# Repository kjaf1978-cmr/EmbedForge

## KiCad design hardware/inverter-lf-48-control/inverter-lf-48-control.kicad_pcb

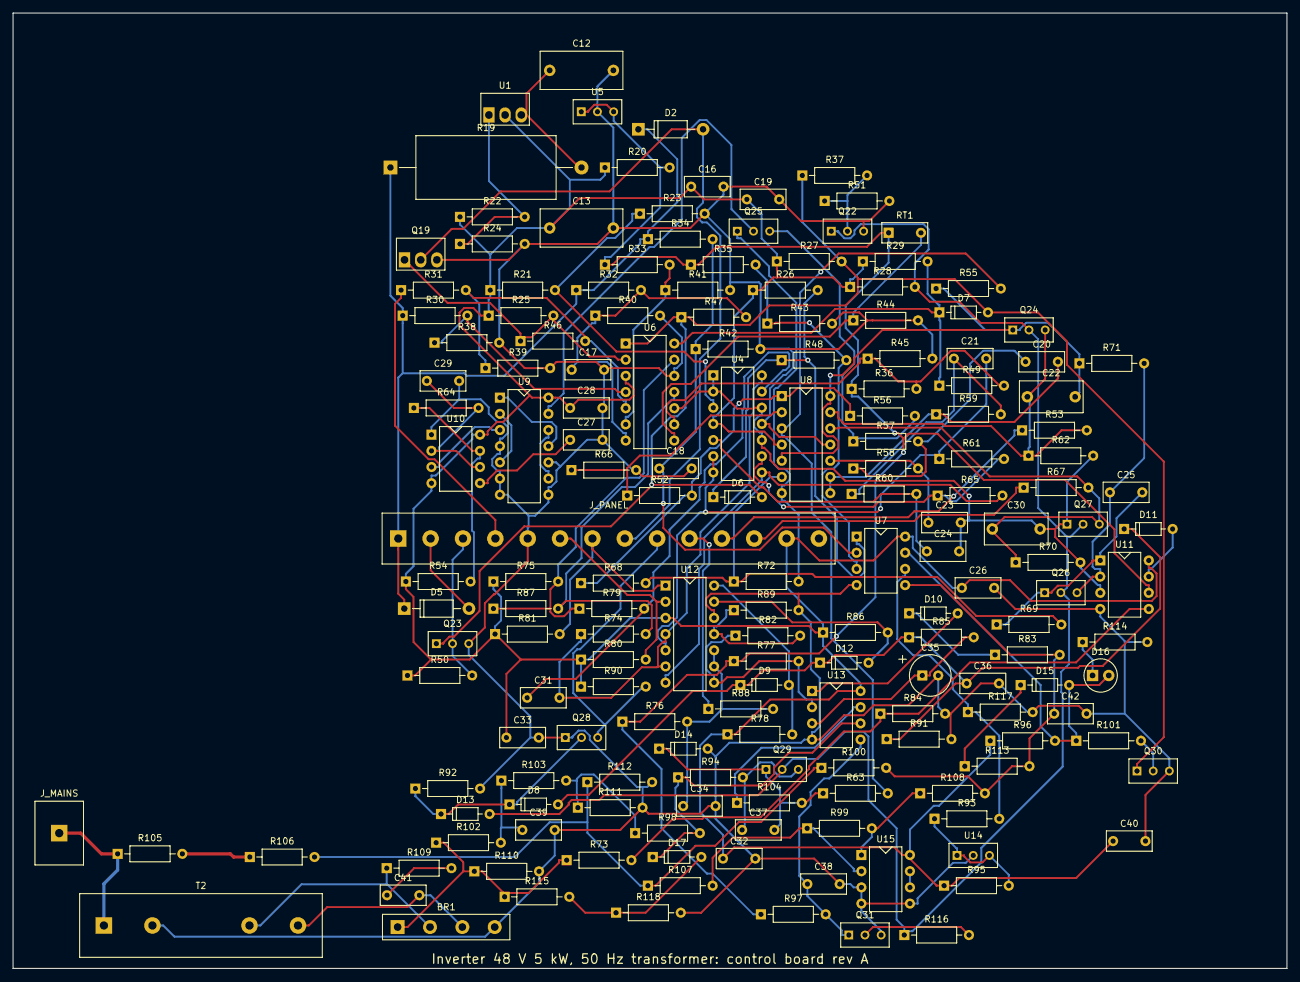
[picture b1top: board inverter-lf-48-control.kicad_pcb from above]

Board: 2 copper layers, 200.0 x 150.0 mm, 172 parts (0 on the bottom side), 101 nets.

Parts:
BR1: DB107; Bridge_Inline_4
C12: 2.2u; C_Film_P10
C13: 10u; C_Film_P10
C16, C19, C23, C26, C28, C29, C32, C33, C40, C41: 100n; C_Disc_5.08
C17, C18, C38: 470n; C_Disc_5.08
C20: 110n; C_Disc_5.08
C21: 270n; C_Disc_5.08
C22, C30: 3.3u; C_Film_P7.5
C24: 39n; C_Disc_5.08
C25, C39, C42: 1u; C_Disc_5.08
C27: 10n; C_Disc_5.08
C31: 3.3n; C_Disc_5.08
C34: 47p; C_Disc_5.08
C35: 22u; CP_Radial_D6.3
C36: 150p; C_Disc_5.08
C37: 220n; C_Disc_5.08
D2, D5: 1N4007; D_DO-41
D6, D7, D8, D9, D10, D11, D12, D13, D15, D17: 1N4148; D_DO-35
D14: BZX55C3V3; D_DO-35
D16: red; LED_D5.0
J_MAINS: mains to the panel; TerminalBlock_1x1_P7.62
J_PANEL: to the panel; TerminalBlock_1x14
Q19: IRF540N; TO-220_Vertical
Q22, Q23, Q30, Q31: BC547B; TO-92_Wide
Q24, Q25, Q26, Q27, Q28, Q29: 2N7000; TO-92_Wide
R19: 220; R_Cement_5W
R20, R78, R86, R95, R96: 2.2k; R_Axial_0207
R21, R23, R25, R26, R27, R28, R29, R38, R39, R40, R41, R42, R43, R44, R54, R61, R65, R66, R68, R69, R72, R74, R84, R88, R90, R101, R102, R112, R113, R117, R118: 10k; R_Axial_0207
R22: 240; R_Axial_0207
R24: 2.05k; R_Axial_0207
R30, R32, R63, R100: 200k; R_Axial_0207
R31: 182k; R_Axial_0207
R33: 1.54k; R_Axial_0207
R34: 243k; R_Axial_0207
R35: 715; R_Axial_0207
R36: 3.92k; R_Axial_0207
R37, R51, R62, R70, R94: 47k; R_Axial_0207
R45: 40.2k; R_Axial_0207
R46: 1M; R_Axial_0207
R47: 475k; R_Axial_0207
R48, R55, R91, R92, R97, R98, R99, R107, R108, R116: 100k; R_Axial_0207
R49: 2.2M; R_Axial_0207
R50: 22k; R_Axial_0207
R52: 4.99k; R_Axial_0207
R53, R67, R105, R106: 470k; R_Axial_0207
R56, R109: 220; R_Axial_0207
R57, R58, R59, R60: 22.1k; R_Axial_0207
R64: 30.9k; R_Axial_0207
R71: 33k; R_Axial_0207
R73: 54.9k; R_Axial_0207
R75, R104, R110: 1k; R_Axial_0207
R76: 90.9k; R_Axial_0207
R77: 86.6k; R_Axial_0207
R79: 13.3k; R_Axial_0207
R80, R81, R83, R114: 4.7k; R_Axial_0207
R82: 7.5k; R_Axial_0207
R85: 220k; R_Axial_0207
R87: 38.3k; R_Axial_0207
R89: 6.19k; R_Axial_0207
R93: 21.5k; R_Axial_0207
R103: 57.6k; R_Axial_0207
R111: 25.5k; R_Axial_0207
R115: 47.5k; R_Axial_0207
RT1: 10k; RT_Disc_5.08
T2: 0.052; Transformer_Wires_P7.62
U1: LM317HV; TO-220_Vertical
U4, U8: TL074; DIP-14
U5: TL431B; TO-92_Wide
U6, U12: LM339; DIP-14
U7: LM393; DIP-8
U9: V12; DIP-14
U10: NE555; DIP-8
U11, U13, U15: LM358; DIP-8
U14: TL431; TO-92_Wide

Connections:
ADJ: R22.2, R24.1, U1.1
AXA: D2.1, D5.1, J_PANEL.1, R19.1, R30.1, R32.1, R34.1
BF: D5.2, J_PANEL.2
BFL: Q30.2, R101.2
BKA: J_PANEL.3, Q23.2, R50.2
BQE: Q22.2, R37.2, R51.1
BSS: Q31.2, R116.2
BUS: J_PANEL.4, R31.1
C200: U9.3, U10.3
D50: R54.2, R64.1, U10.7
DV1: R105.2, R106.1
DVN: R100.1, R106.2, R107.1, R112.1
EN: D6.2, D7.2, Q23.1, Q30.1, R27.2, R37.1, R47.1, U6.1
ENN: D13.2, Q22.1, Q24.2, Q26.2, Q27.2, Q29.2, R28.2, R116.1
F1A: C20.1, R57.2, R58.1
F1B: C23.1, R58.2, U8.10
F1O: C20.2, R59.1, U8.8, U8.9
F2A: C21.1, R59.2, R60.1
F2B: C24.1, R60.2, U4.5
FEA: C37.1, Q29.3, R94.2
FLT: D15.2, D16.2, R96.2, R101.1, U7.7
GND: BR1.4, C12.2, C13.2, C16.2, C17.2, C18.2, C19.2, C26.2, C27.2, C28.2, C29.2, C32.2, C33.2, C34.2, C35.2, C36.2, C38.2, C39.2, C40.2, C42.2, D14.2, J_PANEL.5, Q19.3, Q22.3, Q23.3, Q28.1, Q30.3, Q31.3, R23.2, R24.2, R38.2, R39.2, R40.2, R41.2, R42.2, R43.2, R44.2, R45.2, R51.2, R66.2, R84.2, R89.2, R91.2, R92.2, R110.2, R111.2, R112.2, R114.2, R117.2, R118.2, T2.2, U4.11, U5.2, U6.12, U7.4, U8.11, U9.4, U9.6, U9.7, U9.8, U9.10, U10.1, U11.4, U12.12, U13.4, U14.2, U15.3, U15.4, U15.5
H: R52.2, R56.1, R68.1, U8.1
HN: R52.1, R66.1, U8.2
HP: R55.2, R63.2, U8.3
HVN: D6.1, R26.2, R48.1, U7.1
INA: J_PANEL.6, R80.2, U12.2
INB: J_PANEL.7, R81.2, U12.1
K50: C27.1, U10.5
KC: D2.2, J_PANEL.8, Q19.2
KEN: Q19.1, R25.2, R46.1, U6.2
L: Q25.1, R72.2, U8.7
LAT: D15.1, R113.1
LFA: D16.1, R114.1
LN: R68.2, R69.2, R72.1, U8.6
NDC: C22.1, Q24.3, R53.2, R62.1, U8.13
NEA: D17.1, R94.1, R98.2, U13.6
NFX: C25.1, Q26.3, R71.2, U11.2
NHS: R44.1, RT1.2, U6.8
NSB: R61.2, R65.1, U4.9
NTI: C31.1, R79.2, U4.13
OCH: R77.2, R82.1, U12.8, U13.2
OCL: R82.2, R89.1, U12.11
OCN: D12.2, R86.2, U12.13
OCP: D9.2, R78.2, U12.14
OCS: C36.1, D8.2, D9.1, D11.1, D12.1, R85.1, R91.1
OLC: C35.1, R85.2, U13.3
OLO: D10.2, U13.1
OLS: D10.1, R83.1
OUTL: J_MAINS.1, R105.1, T2.1
OVC: D11.2, U11.7
PDC: C30.1, Q27.3, R67.2, R70.1, U8.12
PLA: D17.2, R115.2, R118.1
PRN: R99.1, R107.2, U15.2
PRO: R99.2, R108.1, U15.1
PST: R74.2, R87.2, U6.11
Q50: Q25.2, U9.13
Q50N: U9.9, U9.12
Q100: U9.1, U9.11
Q100N: U9.2, U9.5
SAO: BR1.2, R109.1, T2.3
SBO: BR1.3, C41.2, T2.4
SD: J_PANEL.9, Q28.3, R90.2
SINE: C21.2, R61.1, U4.6, U4.7, U12.5
SINEB: R65.2, U4.8, U12.7
SNO: C41.1, R109.2
SO: R98.1, R103.2, R111.1
SP: C42.1, R83.2, R100.2, R108.2, R113.2, U7.5
SPRO: U15.6, U15.7
SQ: Q25.3, R56.2, R57.1
SQT: R75.2, R79.1, R87.1, U6.13
SRC: J_PANEL.10, R88.1
SRS: C34.1, R76.2, R88.2, U12.9, U12.10
STOP: D8.1, D13.1, Q28.2, R92.1
SWA: J_PANEL.11, R53.1
SWB: J_PANEL.12, R67.1
T50: C29.1, R64.2, U10.2, U10.6
T90: R36.2, R45.1, R49.2, U6.9
THN: D7.1, R29.2, R49.1, U6.14
TRI: C31.2, R74.1, U4.14, U12.4, U12.6
V12: C13.1, C16.1, C19.1, C26.1, C28.1, C32.1, C33.1, C40.1, J_PANEL.13, R20.1, R21.1, R22.1, R25.1, R26.1, R27.1, R28.1, R29.1, R50.1, R54.1, R75.1, R78.1, R80.1, R81.1, R86.1, R90.1, R95.1, R96.1, U1.2, U4.4, U6.3, U7.8, U8.4, U9.14, U10.4, U10.8, U11.8, U12.3, U13.8, U15.8
VA: C37.2, D14.1, Q29.1, R63.1, R104.2
VAO: R104.1, U13.7
VBF: R30.2, R38.1, U6.4
VBH: C18.1, R34.2, R42.1, U7.2
VBS: C17.1, R32.2, R40.1, R47.2, U6.7
VBU: R31.2, R39.1, R46.2, U6.5
VFX: C25.2, Q26.1, R69.1, U11.1
VHI: R35.2, R43.1, R48.2, U7.3
VLC: R73.2, R84.1, U11.5
VLO: R33.2, R41.1, U6.6
VME: C22.2, Q24.1, R55.1, R71.1, U8.5, U8.14
VMID: C23.2, C24.2, C30.2, Q27.1, R62.2, R70.2, U4.1, U4.2, U4.10, U4.12, U6.10, U11.3
VMR: R21.2, R23.1, U4.3
VRAW: C12.1, R19.2, U1.3
VREF: R20.2, R33.1, R35.1, R36.1, R76.1, R77.1, R97.1, RT1.1, U5.1, U5.3, U11.6
VREF2: R93.1, R95.2, U14.1, U14.3
VRO: BR1.1, R73.1, R102.1, R110.1, R115.1
VRP: R93.2, R117.1, U7.6
VSO: C39.1, R102.2, R103.1
VSS: C38.1, Q31.1, R97.2, U13.5

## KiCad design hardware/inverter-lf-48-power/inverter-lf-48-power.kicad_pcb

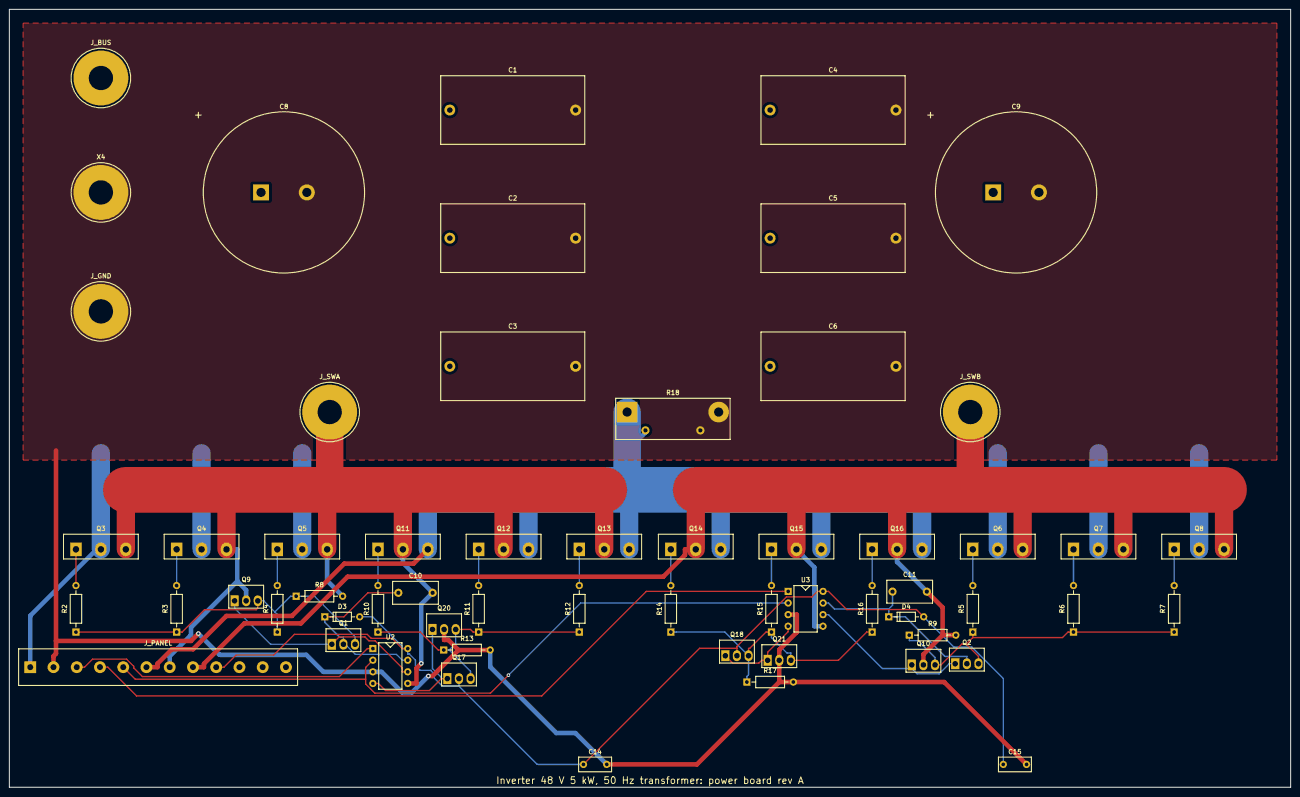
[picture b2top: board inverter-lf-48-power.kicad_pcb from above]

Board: 2 copper layers, 280.0 x 170.0 mm, 59 parts (0 on the bottom side), 31 nets.

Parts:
C1, C2, C3, C4, C5, C6: 47u; C_Film_P27.5
C8, C9: 2200u; CP_SnapIn_D35
C10, C11: 2.2u; C_Film_P7.5
C14, C15: 1u; C_Disc_5.08
D3, D4: 1N4148; D_DO-35
J_BUS: BUS; Lug_M5
J_GND: GND; Lug_M5
J_PANEL: to the panel; TerminalBlock_1x12
J_SWA: SWA; Lug_M5
J_SWB: SWB; Lug_M5
Q1, Q2, Q17, Q18: D44H11; TO-220_Vertical
Q3, Q4, Q5, Q6, Q7, Q8, Q11, Q12, Q13, Q14, Q15, Q16: IRFP4468; TO-247_Vertical
Q9, Q10, Q20, Q21: D45H11; TO-220_Vertical
R2, R3, R4, R5, R6, R7, R10, R11, R12, R14, R15, R16: 4.7; R_Axial_0207
R8, R9, R13, R17: 10k; R_Axial_0207
R18: 0.2m; R_Shunt_4T
U2, U3: IR2184-type 600 V; DIP-8
X4: BAT-; Lug_M5

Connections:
BUS: C1.1, C2.1, C3.1, C4.1, C5.1, C6.1, C8.1, C9.1, J_BUS.1, J_PANEL.1, Q3.2, Q4.2, Q5.2, Q6.2, Q7.2, Q8.2
EHA: Q1.3, Q9.3, R2.1, R3.1, R4.1, R8.1
EHB: Q2.3, Q10.3, R5.1, R6.1, R7.1, R9.1
ELA: Q17.3, Q20.3, R10.1, R11.1, R12.1, R13.1
ELB: Q18.3, Q21.3, R14.1, R15.1, R16.1, R17.1
GHA1: Q3.1, R2.2
GHA2: Q4.1, R3.2
GHA3: Q5.1, R4.2
GHB1: Q6.1, R5.2
GHB2: Q7.1, R6.2
GHB3: Q8.1, R7.2
GLA1: Q11.1, R10.2
GLA2: Q12.1, R11.2
GLA3: Q13.1, R12.2
GLB1: Q14.1, R14.2
GLB2: Q15.1, R15.2
GLB3: Q16.1, R16.2
GND: C1.2, C2.2, C3.2, C4.2, C5.2, C6.2, C8.2, C9.2, C14.2, C15.2, J_GND.1, J_PANEL.2, Q20.2, Q21.2, R13.2, R17.2, R18.2, R18.4, U2.3, U3.3, X4.1
HOA: Q1.1, Q9.1, U2.6
HOB: Q2.1, Q10.1, U3.6
INA: J_PANEL.3, U2.1
INB: J_PANEL.4, U3.1
LOA: Q17.1, Q20.1, U2.4
LOB: Q18.1, Q21.1, U3.4
SD: J_PANEL.5, U2.2, U3.2
SRC: J_PANEL.6, Q11.3, Q12.3, Q13.3, Q14.3, Q15.3, Q16.3, R18.1, R18.3
SWA: C10.2, J_PANEL.7, J_SWA.1, Q3.3, Q4.3, Q5.3, Q9.2, Q11.2, Q12.2, Q13.2, R8.2, U2.5
SWB: C11.2, J_PANEL.8, J_SWB.1, Q6.3, Q7.3, Q8.3, Q10.2, Q14.2, Q15.2, Q16.2, R9.2, U3.5
V12: C14.1, C15.1, D3.2, D4.2, J_PANEL.9, Q17.2, Q18.2, U2.8, U3.8
VBA: C10.1, D3.1, Q1.2, U2.7
VBB: C11.1, D4.1, Q2.2, U3.7

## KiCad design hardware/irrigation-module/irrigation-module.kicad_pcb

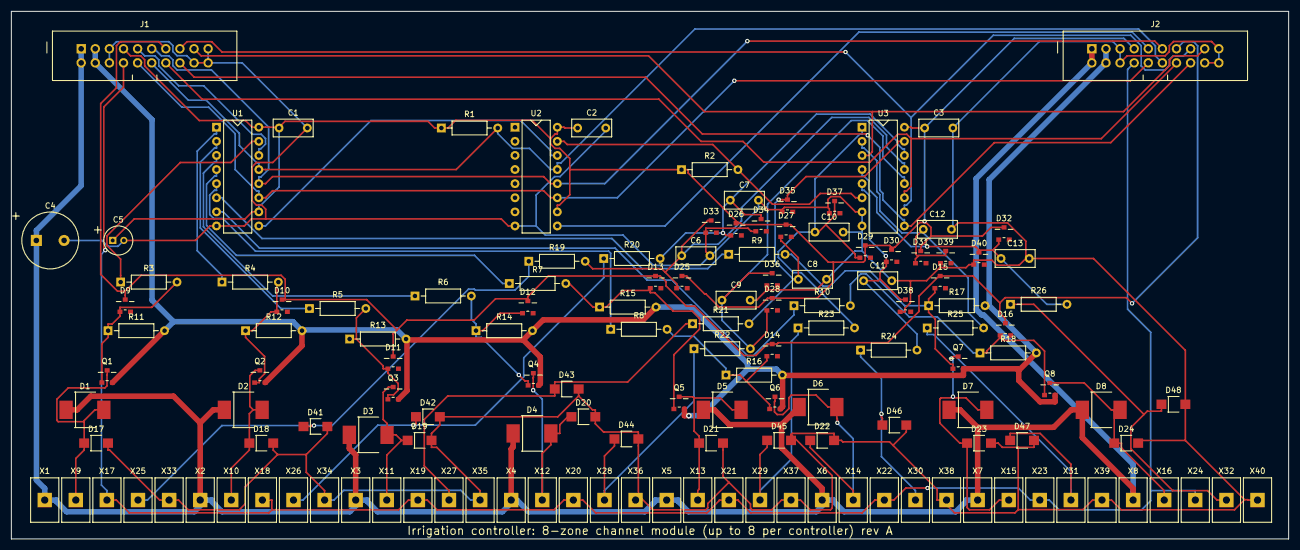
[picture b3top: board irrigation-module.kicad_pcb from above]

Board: 2 copper layers, 230.0 x 95.0 mm, 140 parts (0 on the bottom side), 57 nets.

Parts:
C1, C2, C3, C6, C7, C8, C9, C10, C11, C12, C13: 100n; C_Disc_5.08
C4: 47u; CP_Radial_D10
C5: 10u; CP_Radial_D5
D1, D2, D3, D4, D5, D6, D7, D8: SS34; D_SMC
D9, D10, D11, D12, D13, D14, D15, D16, D25, D26, D27, D28, D29, D30, D31, D32, D33, D34, D35, D36, D37, D38, D39, D40: BAT54; SOT-23
D17, D18, D19, D20, D21, D22, D23, D24: SMAJ33A; D_SMA
D41, D42, D43, D44, D45, D46, D47, D48: SMAJ5.0A; D_SMA
J1, J2: IDC 2x10; IDC_Header_2x10
Q1, Q2, Q3, Q4, Q5, Q6, Q7, Q8: IRLML0060; SOT-23
R1: 1M; R_Axial_0207
R2, R11, R12, R13, R14, R15, R16, R17, R18, R19, R20, R21, R22, R23, R24, R25, R26: 10k; R_Axial_0207
R3, R4, R5, R6, R7, R8, R9, R10: 1k; R_Axial_0207
U1, U2: 74HC595; DIP-16
U3: 74HC4051; DIP-16
X1: valve 1 +24 V; TerminalBlock_1x1
X2: valve 2 +24 V; TerminalBlock_1x1
X3: valve 3 +24 V; TerminalBlock_1x1
X4: valve 4 +24 V; TerminalBlock_1x1
X5: valve 5 +24 V; TerminalBlock_1x1
X6: valve 6 +24 V; TerminalBlock_1x1
X7: valve 7 +24 V; TerminalBlock_1x1
X8: valve 8 +24 V; TerminalBlock_1x1
X9: valve 1; TerminalBlock_1x1
X10: valve 2; TerminalBlock_1x1
X11: valve 3; TerminalBlock_1x1
X12: valve 4; TerminalBlock_1x1
X13: valve 5; TerminalBlock_1x1
X14: valve 6; TerminalBlock_1x1
X15: valve 7; TerminalBlock_1x1
X16: valve 8; TerminalBlock_1x1
X17: sensor 1 +3.3 V; TerminalBlock_1x1
X18: sensor 2 +3.3 V; TerminalBlock_1x1
X19: sensor 3 +3.3 V; TerminalBlock_1x1
X20: sensor 4 +3.3 V; TerminalBlock_1x1
X21: sensor 5 +3.3 V; TerminalBlock_1x1
X22: sensor 6 +3.3 V; TerminalBlock_1x1
X23: sensor 7 +3.3 V; TerminalBlock_1x1
X24: sensor 8 +3.3 V; TerminalBlock_1x1
X25: sensor 1 out; TerminalBlock_1x1
X26: sensor 2 out; TerminalBlock_1x1
X27: sensor 3 out; TerminalBlock_1x1
X28: sensor 4 out; TerminalBlock_1x1
X29: sensor 5 out; TerminalBlock_1x1
X30: sensor 6 out; TerminalBlock_1x1
X31: sensor 7 out; TerminalBlock_1x1
X32: sensor 8 out; TerminalBlock_1x1
X33: sensor 1 0 V; TerminalBlock_1x1
X34: sensor 2 0 V; TerminalBlock_1x1
X35: sensor 3 0 V; TerminalBlock_1x1
X36: sensor 4 0 V; TerminalBlock_1x1
X37: sensor 5 0 V; TerminalBlock_1x1
X38: sensor 6 0 V; TerminalBlock_1x1
X39: sensor 7 0 V; TerminalBlock_1x1
X40: sensor 8 0 V; TerminalBlock_1x1

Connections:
A0: J1.14, J2.14, U3.11
A1: J1.15, J2.15, U3.10
A2: J1.16, J2.16, U3.9
ANA: J1.17, J2.17, U3.3
G1: D9.1, Q1.1, R3.2, R11.1
G2: D10.1, Q2.1, R4.2, R12.1
G3: D11.1, Q3.1, R5.2, R13.1
G4: D12.1, Q4.1, R6.2, R14.1
G5: D13.1, Q5.1, R7.2, R15.1
G6: D14.1, Q6.1, R8.2, R16.1
G7: D15.1, Q7.1, R9.2, R17.1
G8: D16.1, Q8.1, R10.2, R18.1
GCL: D9.3, D10.3, D11.3, D12.3, D13.3, D14.3, D15.3, D16.3, J1.13, J2.13
GND: C1.2, C2.2, C3.2, C4.2, C5.2, C6.2, C7.2, C8.2, C9.2, C10.2, C11.2, C12.2, C13.2, D17.2, D18.2, D19.2, D20.2, D21.2, D22.2, D23.2, D24.2, D33.1, D34.1, D35.1, D36.1, D37.1, D38.1, D39.1, D40.1, D41.2, D42.2, D43.2, D44.2, D45.2, D46.2, D47.2, D48.2, J1.5, J1.6, J1.18, J1.19, J1.20, J2.5, J2.6, J2.18, J2.19, J2.20, U1.8, U2.8, U3.7, U3.8, X33.1, X34.1, X35.1, X36.1, X37.1, X38.1, X39.1, X40.1
MX1: C6.1, D25.1, D33.3, R19.2, U3.13
MX2: C7.1, D26.1, D34.3, R20.2, U3.14
MX3: C8.1, D27.1, D35.3, R21.2, U3.15
MX4: C9.1, D28.1, D36.3, R22.2, U3.12
MX5: C10.1, D29.1, D37.3, R23.2, U3.1
MX6: C11.1, D30.1, D38.3, R24.2, U3.5
MX7: C12.1, D31.1, D39.3, R25.2, U3.2
MX8: C13.1, D32.1, D40.3, R26.2, U3.4
MXEN: R2.2, U2.15, U3.6
OE: J1.12, J2.12, R1.2, U1.13, U2.13
OUT1: D1.2, D17.1, Q1.3, X9.1
OUT2: D2.2, D18.1, Q2.3, X10.1
OUT3: D3.2, D19.1, Q3.3, X11.1
OUT4: D4.2, D20.1, Q4.3, X12.1
OUT5: D5.2, D21.1, Q5.3, X13.1
OUT6: D6.2, D22.1, Q6.3, X14.1
OUT7: D7.2, D23.1, Q7.3, X15.1
OUT8: D8.2, D24.1, Q8.3, X16.1
Q1: R3.1, U1.15
Q2: R4.1, U1.1
Q3: R5.1, U1.2
Q4: R6.1, U1.3
Q5: R7.1, U1.4
Q6: R8.1, U1.5
Q7: R9.1, U1.6
Q8: R10.1, U1.7
RCLK: J1.11, J2.11, U1.12, U2.12
SEN1: D41.1, R19.1, X25.1
SEN2: D42.1, R20.1, X26.1
SEN3: D43.1, R21.1, X27.1
SEN4: D44.1, R22.1, X28.1
SEN5: D45.1, R23.1, X29.1
SEN6: D46.1, R24.1, X30.1
SEN7: D47.1, R25.1, X31.1
SEN8: D48.1, R26.1, X32.1
SER: J1.9, U1.14
SO: J2.9, U2.9
SR2: U1.9, U2.14
SRCLK: J1.10, J2.10, U1.11, U2.11
SRET: J1.3, J1.4, J2.3, J2.4, Q1.2, Q2.2, Q3.2, Q4.2, Q5.2, Q6.2, Q7.2, Q8.2, R11.2, R12.2, R13.2, R14.2, R15.2, R16.2, R17.2, R18.2
V24: C4.1, D1.1, D2.1, D3.1, D4.1, D5.1, D6.1, D7.1, D8.1, J1.1, J1.2, J2.1, J2.2, X1.1, X2.1, X3.1, X4.1, X5.1, X6.1, X7.1, X8.1
V33: C1.1, C2.1, C3.1, C5.1, D25.3, D26.3, D27.3, D28.3, D29.3, D30.3, D31.3, D32.3, J1.7, J2.7, R1.1, R2.1, U1.10, U1.16, U2.10, U2.16, U3.16
V33S: J1.8, J2.8, X17.1, X18.1, X19.1, X20.1, X21.1, X22.1, X23.1, X24.1

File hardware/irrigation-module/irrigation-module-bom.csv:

"on this board","qty","references","part","value","details","footprint","MPN","maker","distributors (order numbers)","unit EUR","total EUR","price basis"
"yes","11","C1 C2 C3 C6 C7 C8 C9 C10 C11 C12 C13","Capacitor","100 nF","voltage rating 50 V","C_Disc_5.08","ceramic X7R or MKT 100nF 50 V, 5.08 mm","KEMET / Vishay","any distributor (5.08 mm)","0.12","1.32","estimate"
"yes","1","C4","Electrolytic capacitor","47 µF","voltage rating 50 V","CP_Radial_D10","47uF 50 V 105 °C (e.g. Panasonic FC series)","Panasonic / Nichicon","any distributor (radial)","0.10","0.10","estimate"
"yes","1","C5","Electrolytic capacitor","10 µF","voltage rating 16 V","CP_Radial_D5","10uF 16 V 105 °C (e.g. Panasonic FC series)","Panasonic / Nichicon","any distributor (radial)","0.10","0.10","estimate"
"yes","8","D1 D2 D3 D4 D5 D6 D7 D8","Diode","SS34","","D_SMC","SS34","various","LCSC C8678","0.10","0.80","estimate"
"yes","24","D9 D10 D11 D12 D13 D14 D15 D16 D25 D26 D27 D28 D29 D30 D31 D32 D33 D34 D35 D36 D37 D38 D39 D40","Diode","BAT54","","SOT-23","BAT54","various","LCSC C47546","0.05","1.20","estimate"
"yes","8","D17 D18 D19 D20 D21 D22 D23 D24","TVS diode","SMAJ33A","","D_SMA","SMAJ33A","Littelfuse","LCSC; Mouser","0.20","1.60","estimate"
"yes","8","D41 D42 D43 D44 D45 D46 D47 D48","TVS diode","SMAJ5.0A","","D_SMA","SMAJ5.0A","Littelfuse","LCSC; Mouser","0.20","1.60","estimate"
"yes","2","J1 J2","Box header 2 × 10 (IDC ribbon cable)","IDC 2×10","","IDC_Header_2x10","61202021621 (WR-BHD)","Würth Elektronik","Mouser 710-61202021621; Digi-Key","0.60","1.20","estimate"
"yes","8","Q1 Q2 Q3 Q4 Q5 Q6 Q7 Q8","N-channel MOSFET","IRLML0060","","SOT-23","IRLML0060TRPBF","Infineon","Mouser; Digi-Key","0.45","3.60","estimate"
"yes","1","R1","Resistor","1 MΩ","power rating 250 mW","R_Axial_0207","metal film 1MΩ 0.6 W, 1 %, 50 ppm/K (e.g. Vishay MBB0207)","Vishay / Yageo","any distributor (0207 1 %)","0.08","0.08","estimate"
"yes","17","R2 R11 R12 R13 R14 R15 R16 R17 R18 R19 R20 R21 R22 R23 R24 R25 R26","Resistor","10 kΩ","power rating 250 mW","R_Axial_0207","metal film 10kΩ 0.6 W, 1 %, 50 ppm/K (e.g. Vishay MBB0207)","Vishay / Yageo","any distributor (0207 1 %)","0.08","1.36","estimate"
"yes","8","R3 R4 R5 R6 R7 R8 R9 R10","Resistor","1 kΩ","power rating 250 mW","R_Axial_0207","metal film 1kΩ 0.6 W, 1 %, 50 ppm/K (e.g. Vishay MBB0207)","Vishay / Yageo","any distributor (0207 1 %)","0.08","0.64","estimate"
"yes","2","U1 U2","8-bit shift register with output latch (74HC595)","74HC595","","DIP-16","SN74HC595N","Texas Instruments","Mouser 595-SN74HC595N; LCSC","0.55","1.10","estimate"
"yes","1","U3","8-channel analogue multiplexer (74HC4051)","74HC4051","","DIP-16","SN74HC4051N","Texas Instruments","Mouser 595-SN74HC4051N; LCSC","0.55","0.55","estimate"
"yes","40","X1 X2 X3 X4 X5 X6 X7 X8 X9 X10 X11 X12 X13 X14 X15 X16 X17 X18 X19 X20 X21 X22 X23 X24 X25 X26 X27 X28 X29 X30 X31 X32 X33 X34 X35 X36 X37 X38 X39 X40","Screw terminal","5.08 mm, 1 pole","functions: valve 1, valve 1 +24 V, valve 2, valve 2 +24 V, valve 3, valve 3 +24 V, valve 4, valve 4 +24 V, valve 5, valve 5 +24 V, valve 6, valve 6 +24 V, valve 7, valve 7 +24 V, valve 8, valve 8 +24 V, sensor 1 out, sensor 1 +3.3 V, sensor 1 0 V, sensor 2 out, sensor 2 +3.3 V, sensor 2 0 V, sensor 3 out, sensor 3 +3.3 V, sensor 3 0 V, sensor 4 out, sensor 4 +3.3 V, sensor 4 0 V, sensor 5 out, sensor 5 +3.3 V, sensor 5 0 V, sensor 6 out, sensor 6 +3.3 V, sensor 6 0 V, sensor 7 out, sensor 7 +3.3 V, sensor 7 0 V, sensor 8 out, sensor 8 +3.3 V, sensor 8 0 V","TerminalBlock_1x1","MKDS 1,5/ 2-5,08 (2 poles per block)","Phoenix Contact","RS 193-0564","0.40","16.00","estimate"

"Parts on this board: EUR 31.25 (unit quantity). Indicative prices, October 2026, EUR without VAT (converted at USD × 0.9, GBP × 1.15): ""live"" from a distributor page or snapshot, ""estimate"" a typical price. Check prices, stock and lead times when ordering; wholesale prices of contactors and breakers are often 40–60 % below distributor list prices."

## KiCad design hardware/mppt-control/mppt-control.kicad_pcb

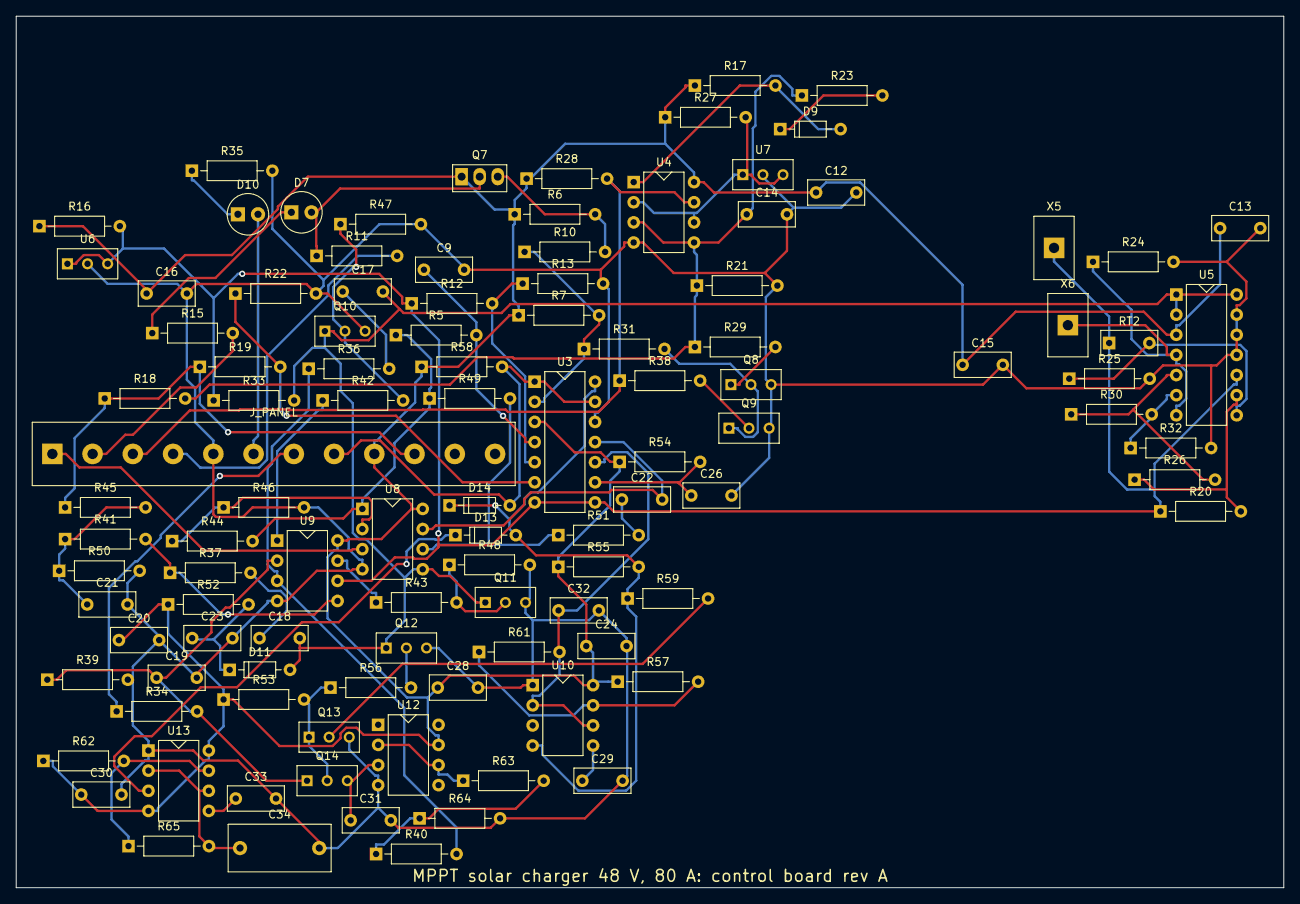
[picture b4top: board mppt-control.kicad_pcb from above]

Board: 2 copper layers, 160.0 x 110.0 mm, 107 parts (0 on the bottom side), 63 nets.

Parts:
C9, C12, C13, C15, C16, C20, C22, C24, C28, C30: 100n; C_Disc_5.08
C14, C23, C31: 1u; C_Disc_5.08
C17, C26: 220n; C_Disc_5.08
C18, C19, C21, C29, C32, C33: 10n; C_Disc_5.08
C34: 4.7u; C_Film_P10
D7: green; LED_D5.0
D9, D11, D13, D14: 1N4148; D_DO-35
D10: red; LED_D5.0
J_PANEL: to the panel; TerminalBlock_1x12
Q7: BD140; TO-126_Vertical
Q8, Q9, Q10, Q11, Q12, Q13: BC547B; TO-92_Wide
Q14: 2N7000; TO-92_Wide
R5, R6, R7, R10, R21, R22, R24, R25, R29, R32, R33, R39, R40, R41, R42, R43, R49, R51, R53, R55, R56, R59, R64: 10k; R_Axial_0207
R11, R23, R47, R48: 47k; R_Axial_0207
R12: 27k; R_Axial_0207
R13: 3.3k; R_Axial_0207
R15, R17, R36, R52, R58: 4.7k; R_Axial_0207
R16, R27, R35, R46: 1k; R_Axial_0207
R18: 221k; R_Axial_0207
R19: 226k; R_Axial_0207
R20: 3.74k; R_Axial_0207
R26: 7.87k; R_Axial_0207
R28: 2.2k; R_Axial_0207
R30: 22.1k; R_Axial_0207
R31, R38: 100k; R_Axial_0207
R34: 365k; R_Axial_0207
R37: 470k; R_Axial_0207
R44: 30k; R_Axial_0207
R45: 232k; R_Axial_0207
R50: 10.7k; R_Axial_0207
R54: 1M; R_Axial_0207
R57: 6.8k; R_Axial_0207
R61: 330; R_Axial_0207
R62: 3.01M; R_Axial_0207
R63: 2.1k; R_Axial_0207
R65: 15k; R_Axial_0207
RT2: 10k; RT_Disc_5.08
U3, U5: LM339; DIP-14
U4: LM393; DIP-8
U6, U7: TL431; TO-92_Wide
U8, U9: LM358; DIP-8
U10, U13: NE555; DIP-8
U12: TL071; DIP-8
X5, X6: NTC bat.; TerminalBlock_1x1

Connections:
BCV: Q11.2, R43.2, R48.1
BDN: R7.2, R10.1, R31.1, U3.2
BF: J_PANEL.1, U8.3
BMP: Q10.2, R42.2, R47.1
BN: J_PANEL.2, R15.2
BNC: Q8.2, Q9.1, R31.2
BNL: Q9.2, R38.2
BP: Q13.2, R59.2
BQD: Q7.3, R6.2, R10.2
BZ: Q12.2, R56.2
CH: C31.1, Q14.3, U12.3
CNC: Q8.1, R29.2
CTL: C29.1, U10.5
DIS: R57.2, R61.1, U10.7
ECV: R43.1, U9.7
EMP: R42.1, U9.1
FCV: C18.1, R37.2
FI: C22.1, R51.2
FLT: D9.2, R17.2, U4.1
FLT2: J_PANEL.3, R28.2, R38.1, U4.7
FMP: C17.1, R36.2
GB: J_PANEL.4, R11.2
GD: D7.2, Q7.2, R11.1
GND: C9.2, C12.2, C13.2, C14.2, C15.2, C16.2, C19.2, C20.2, C21.2, C23.2, C24.2, C26.2, C28.2, C29.2, C30.2, C31.2, C32.2, C33.2, C34.2, J_PANEL.5, Q8.3, Q9.3, Q10.3, Q11.3, Q12.3, Q13.3, R13.2, R21.2, R22.2, R24.2, R25.2, R32.2, R35.2, R39.2, R46.2, R47.2, R48.2, R50.2, R64.2, U3.12, U4.4, U5.11, U5.12, U5.13, U6.2, U7.2, U8.4, U9.4, U10.1, U12.4, U13.1
IFB: R44.1, R46.1, U8.2
IREF: C17.2, C18.2, D11.2, Q10.1, Q11.1, Q12.1, R33.2, U5.1, U5.2, U5.14, U8.5
ISA: R5.1, R44.2, R49.1, U8.1
ISF: C9.1, R5.2, U3.4
ITH: R12.2, R13.1, U3.5
LAT: D9.1, R23.2
LCA: D7.1, R15.1
LFB: D10.2, J_PANEL.6
LFK: D10.1, R35.1
NBT: R24.1, U5.4, U5.7, X6.1
NCV: R37.1, R41.2, U9.5
NHS: R25.1, RT2.2, U5.8
NI: R49.2, R51.1, U8.6
NMP: R36.1, R40.2, U9.3
POR: C26.1, R54.2, U3.9
PVP: J_PANEL.7, R34.1
PWM: D14.2, J_PANEL.8, R58.2, U3.1, U3.13
RAMP: C32.1, R61.2, U3.10, U10.2, U10.6
RUN: D13.2, D14.1, R55.2, R59.1, U3.14, U10.4
SMP: Q13.1, Q14.2, R53.2, R56.1
SS: C23.1, D11.1, R52.2
T0: R30.2, R32.1, U5.6
T50: R26.2, R30.1, U5.5
T90: R20.2, R26.1, U5.9
TCTL: C33.1, U13.5
TD: R62.2, R65.1, U13.7
TOUT: D13.1, U13.3
TT: C34.1, R65.2, U13.2, U13.6
V12: C12.1, C13.1, C15.1, C16.1, C20.1, C24.1, C28.1, C30.1, J_PANEL.9, Q7.1, R6.1, R7.1, R16.1, R17.1, R27.1, R28.1, R52.1, R53.1, R54.1, R55.1, R57.1, R58.1, R62.1, U3.3, U4.8, U5.3, U8.8, U9.8, U10.8, U12.7, U13.4, U13.8
VBS: C21.1, R41.1, R45.2, R50.1
VCMD: C22.2, U3.11, U8.7
VO: J_PANEL.10, R18.1, R19.1, R45.1
VOCH: R63.1, U12.2, U12.6
VOS2: C14.1, R18.2, R21.1, R23.1, R29.1, U4.3, U4.5
VOS3: R19.2, R22.1, U3.6
VPS: C19.1, Q14.1, R34.2, R39.1, U9.2
VREF: R12.1, R16.2, R20.1, R33.1, RT2.1, U3.7, U3.8, U5.10, U6.1, U6.3, U9.6, X5.1
VREF2: R27.2, U4.2, U4.6, U7.1, U7.3
VSET: R40.1, R63.2, R64.1

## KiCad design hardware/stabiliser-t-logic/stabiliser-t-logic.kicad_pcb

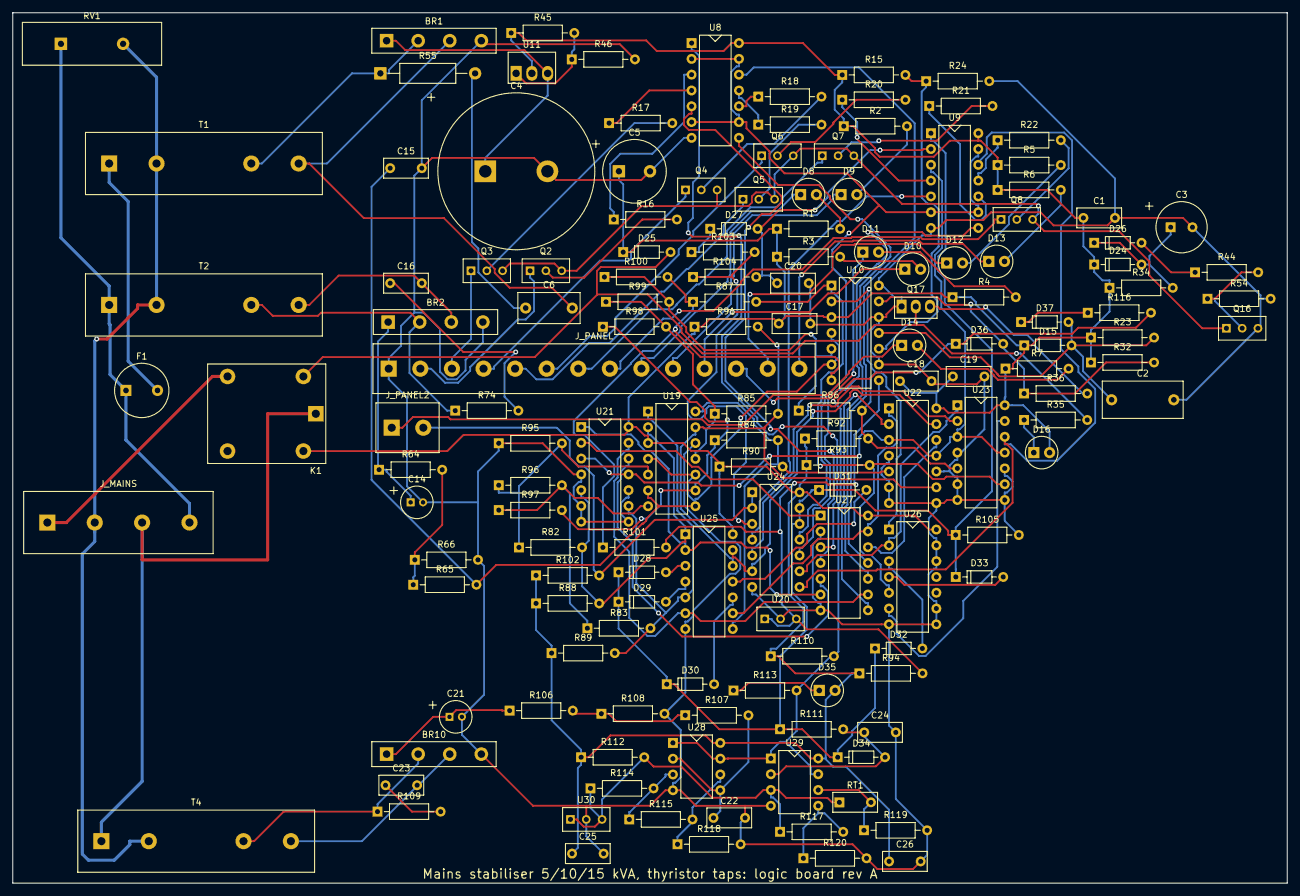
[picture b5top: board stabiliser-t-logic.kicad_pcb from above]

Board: 2 copper layers, 205.0 x 140.0 mm, 149 parts (0 on the bottom side), 122 nets.

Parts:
BR1, BR2, BR10: DB107; Bridge_Inline_4
C1, C16, C17, C18, C19, C23, C25, C26: 100n; C_Disc_5.08
C2: 4.7u; C_Film_P10
C3: 47u; CP_Radial_D8
C4: 2200u; CP_SnapIn_D25
C5: 100u; CP_Radial_D10
C6: 1u; C_Film_P7.5
C14, C21: 4.7u; CP_Radial_D5
C15, C22, C24: 470n; C_Disc_5.08
C20: 22n; C_Disc_5.08
D8, D9, D10, D11, D12, D13, D14: yellow; LED_D5.0
D15, D24, D25, D27, D28, D29, D30, D31, D32, D33, D34, D36, D37: 1N4148; D_DO-35
D16: green; LED_D5.0
D26: BZX55C5V1; D_DO-35
D35: red; LED_D5.0
F1: 0.2; F_TR5
J_MAINS: mains to the panel; TerminalBlock_1x4_P7.62
J_PANEL: to the panel; TerminalBlock_1x14
J_PANEL2: to the panel; TerminalBlock_1x2
K1: 12 V 30 A; Relay_SPDT_SRD
Q2, Q3, Q4, Q5, Q6, Q7, Q8, Q16: BC547B; TO-92_Wide
Q17: BD139; TO-126_Vertical
R1, R2, R3, R4, R5, R6, R7: 680; R_Axial_0207
R15: 2.49k; R_Axial_0207
R16, R17, R18, R19, R20, R21, R22, R24, R34, R66, R104, R108, R110, R118, R120: 10k; R_Axial_0207
R23, R82, R83, R84, R85, R86, R87, R111: 1M; R_Axial_0207
R32, R35, R36, R44, R88, R89, R90, R91, R92, R93, R94, R112, R116: 2.2k; R_Axial_0207
R45: 240; R_Axial_0207
R46: 2.05k; R_Axial_0207
R54, R102: 47k; R_Axial_0207
R55: 47; R_Axial_0309
R64, R106: 68k; R_Axial_0207
R65, R105, R107: 100k; R_Axial_0207
R74, R109: 220; R_Axial_0207
R95: 5.36k; R_Axial_0207
R96, R97, R98, R99: 732; R_Axial_0207
R100: 909; R_Axial_0207
R101: 787; R_Axial_0207
R103: 1k; R_Axial_0207
R113: 4.7k; R_Axial_0207
R114: 1.82k; R_Axial_0207
R115: 3.65k; R_Axial_0207
R117: 7.32k; R_Axial_0207
R119: 1.5k; R_Axial_0207
RT1: 10k; RT_Disc_5.08
RV1: 20D471K; MOV_Disc_20
T1: 0.13; Transformer_Wires_P7.62
T2, T4: 0.052; Transformer_Wires_P7.62
U8, U9, U21, U22, U23, U24, U25, U26, U27: +12V; DIP-14
U10, U19: LM339; DIP-14
U11: LM317HV; TO-220_Vertical
U20, U30: TL431; TO-92_Wide
U28, U29: LM393; DIP-8

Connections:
+12V: C1.1, C5.1, C17.1, C18.1, C19.1, C25.1, C26.1, D15.1, D16.2, D24.1, D25.1, D35.2, K1.1, R1.1, R2.1, R3.1, R4.1, R5.1, R6.1, R7.1, R15.1, R23.1, R32.1, R34.1, R45.1, R88.1, R89.1, R90.1, R91.1, R92.1, R93.1, R94.1, R102.1, R110.1, R112.1, U8.14, U9.14, U10.3, U11.2, U19.3, U21.14, U22.14, U23.14, U24.14, U25.14, U26.14, U27.14, U28.8, U29.8
AA: BR1.2, R55.1, T1.3
AB: BR1.3, C6.2, T1.4
ADJ: R45.2, R46.1, U11.1
ALLOFF: R103.2, R104.1, U24.3
BD: Q17.3, R36.2
BG1: Q2.2, R16.2
BG2: Q3.2, R17.2
BG3: Q4.2, R18.2
BG4: Q5.2, R19.2
BG5: Q6.2, R20.2
BG6: Q7.2, R21.2
BG7: Q8.2, R22.2
BPE: Q16.2, R44.2, R54.1
CHG: D28.1, D29.1, D30.1, D31.1, D32.1, D33.1, D34.1, R105.1, R111.1, U9.1, U24.12, U24.13
CK: U9.3, U21.3, U21.11, U22.3, U22.11, U23.3, U23.11
CPE: C3.1, D24.2, D26.1, R34.2
CST: C24.1, D34.2, R111.2, U29.2
DF2K: D37.1, R116.1
DLY: C2.1, D15.2, D37.2, R23.2, U10.11
DTH: R15.2, R24.1, U10.10
EG: Q2.3, Q3.3, Q4.3, Q5.3, Q6.3, Q7.3, Q8.3, Q16.1
FLTS: D36.1, R110.2, R113.2, R116.2, U28.1, U28.7, U29.1, U29.7
G1: R16.1, U8.3
G2: R17.1, U8.4
G3: R18.1, U8.10
G4: R19.1, U8.11
G5: R20.1, U9.4
G6: R21.1, U9.10
G7: R22.1, U9.11
GND: BR1.4, BR2.4, BR10.4, C1.2, C2.2, C3.2, C4.2, C5.2, C14.2, C15.2, C17.2, C18.2, C19.2, C20.2, C21.2, C22.2, C24.2, C25.2, C26.2, J_PANEL.1, Q16.3, Q17.1, R24.2, R46.2, R54.2, R66.2, R95.1, R105.2, R108.2, R118.2, R119.2, R120.2, U8.7, U9.7, U10.9, U10.12, U10.14, U19.12, U20.2, U21.4, U21.6, U21.7, U21.8, U21.10, U22.4, U22.6, U22.7, U22.8, U22.10, U23.4, U23.6, U23.7, U23.8, U23.10, U24.7, U25.7, U26.7, U26.8, U26.9, U26.12, U26.13, U27.2, U27.7, U28.4, U29.4, U30.2
KD: D25.2, K1.2, Q17.2, R35.2
KMC: J_MAINS.1, K1.5
LFA: D35.1, R113.1
LK1: J_PANEL.2, Q2.1
LK2: J_PANEL.3, Q3.1
LK3: J_PANEL.4, Q4.1
LK4: J_PANEL.5, Q5.1
LK5: J_PANEL.6, Q6.1
LK6: J_PANEL.7, Q7.1
LK7: J_PANEL.8, Q8.1
LKOA: D16.1, R35.1
LN1: U21.2, U27.1
LN2: U21.12, U27.5
LN3: U22.2, U27.8
LN4: U22.12, U27.12
LN5: U23.2, U24.5
LN6: U9.12, U23.12, U24.8
LO1: U21.1, U25.2, U27.6
LO1A: D8.1, J_PANEL.9
LO2: U21.13, U25.6, U27.9
LO2A: D9.1, J_PANEL.10
LO3: U22.1, U25.9, U27.13
LO3A: D10.1, J_PANEL.11
LO4: U22.13, U24.6, U25.13
LO4A: D11.1, J_PANEL.12
LO5: U23.1, U24.9, U26.2
LO5A: D12.1, J_PANEL.13
LO6: U23.13, U26.6
LO6A: D13.1, J_PANEL.14
LO7A: D14.1, J_PANEL2.1
LY1: D8.2, R1.2
LY2: D9.2, R2.2
LY3: D10.2, R3.2
LY4: D11.2, R4.2
LY5: D12.2, R5.2
LY6: D13.2, R6.2
LY7: D14.2, R7.2
N: J_MAINS.2, RV1.2, T1.2, T2.2, T4.2
N1: R82.1, R95.2, R96.1, U19.5
N2: R83.1, R96.2, R97.1, U19.7
N3: R84.1, R97.2, R98.1, U19.9
N4: R85.1, R98.2, R99.1, U19.11
N5: R86.1, R99.2, R100.1, U10.5
N6: R87.1, R100.2, R101.1, U10.7
NCHG: U8.2, U8.6, U8.9, U8.13, U9.6, U9.9, U9.13, U24.11
NHS: R119.1, RT1.2, U29.6
O1: R82.2, R88.2, U19.2, U21.5, U25.1
O2: R83.2, R89.2, U19.1, U21.9, U25.5
O3: R84.2, R90.2, U19.14, U22.5, U25.8
O4: R85.2, R91.2, U19.13, U22.9, U25.12
O5: R86.2, R92.2, U10.2, U23.5, U26.1
O6: R87.2, R93.2, U10.1, U23.9, U26.5
OD: D36.2, R32.2, R36.1, U10.13
OFFN: J_PANEL2.2, R102.2, U24.1, U24.2
S1: U8.1, U27.3
S2: U8.5, U27.4
S3: U8.8, U27.10
S4: U8.12, U27.11
S5: U9.5, U24.4
S6: U9.8, U24.10
SA: BR2.2, R74.1, T2.3
SA2: BR10.2, R109.1, T4.3
SB: BR2.3, C16.2, T2.4
SB2: BR10.3, C23.2, T4.4
SEN2: R106.2, R107.1, R108.1
SENSE: R64.2, R65.1, R66.1
SF: C15.1, R65.2, U10.4, U10.6, U19.4, U19.6, U19.8, U19.10
SF2: C22.1, R107.2, U28.2, U28.5
SN: C16.1, R74.2
SN2: C23.1, R109.2
SN3: C6.1, R55.2
T5: J_MAINS.3, K1.3, T4.1
VF: F1.2, T1.1
VIN: F1.1, J_MAINS.4, RV1.1, T2.1
VOV: R114.2, R115.1, U28.3
VRAW: BR1.1, C4.1, U11.3
VREF: R94.2, R101.2, U10.8, U20.1, U20.3
VREF2: R112.2, R114.1, R117.1, RT1.1, U29.3, U30.1, U30.3
VSR: BR2.1, C14.1, R64.1
VSR2: BR10.1, C21.1, R106.1
VT85: R117.2, R120.1, U29.5
VUV: R115.2, R118.1, U28.6
XC1: D28.2, U25.3
XC2: D29.2, U25.4
XC3: D30.2, U25.10
XC4: D31.2, U25.11
XC5: D32.2, U26.3
XC6: D33.2, U26.4
ZDK: D27.1, R103.1
ZPE: D26.2, R44.1
ZWD: C20.1, D27.2, R104.2, U9.2
